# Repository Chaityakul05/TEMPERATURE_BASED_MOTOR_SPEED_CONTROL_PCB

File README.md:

# Temperature-Based DC Motor Speed Control

## Overview

This project focuses on controlling the speed of a DC motor based on the ambient temperature. The system utilizes a combination of analog and digital components: the **LM35** temperature sensor for temperature measurement, the **LM358** Op-Amp for comparing the sensor output with a reference voltage, the **555 Timer IC** to generate a PWM signal, and the **L293D motor driver** to control the motor's speed. As the temperature increases, the PWM signal's duty cycle increases, causing the motor to run faster.

## Key Components

- **LM35**: A temperature sensor that outputs an analog voltage proportional to the ambient temperature, with a sensitivity of 10 mV per °C.
- **LM358**: An operational amplifier configured as a comparator to compare the temperature sensor's output with a reference voltage set by a **potentiometer**.
- **555 Timer IC**: A timer IC configured in astable mode to generate a continuous PWM signal. The duty cycle of this signal is controlled by the output from the Op-Amp.
- **L293D**: A motor driver IC used to drive the DC motor by adjusting the voltage applied to the motor based on the PWM signal.
- **DC Motor**: The motor whose speed is controlled by the PWM signal generated by the 555 Timer and regulated by the L293D motor driver.
- **Potentiometer**: Used to set the reference voltage for the comparison with the LM35 output, determining the threshold temperature at which the motor speed increases.

## Working Principle

1. **Temperature Measurement**: The **LM35** temperature sensor detects the ambient temperature and generates a voltage output that is linearly proportional to the temperature (e.g., 250 mV at 25°C).
   
2. **Signal Comparison**: The **LM358 Op-Amp** compares the output from the **LM35** with a reference voltage set by the **potentiometer**. When the temperature exceeds the threshold set by the potentiometer, the Op-Amp output switches states.
   
3. **PWM Signal Generation**: The output of the **LM358** Op-Amp is used to control the **555 Timer IC**'s duty cycle. The **555 Timer** generates a PWM signal in astable mode, where the duty cycle is determined by the Op-Amp output. As the temperature rises, the Op-Amp output increases the PWM duty cycle, resulting in a faster motor speed.
   
4. **Motor Speed Control**: The PWM signal generated by the **555 Timer** is fed to the **L293D motor driver**, which adjusts the speed of the **DC motor**. The motor speed increases with higher temperature due to the higher PWM duty cycle.

## Circuit Setup

1. **Temperature Sensing**: The **LM35** is connected to a power supply (typically 5V). Its output is connected to the non-inverting input of the **LM358** Op-Amp.
   
2. **Reference Voltage**: The reference voltage is set using the **potentiometer**. The wiper of the potentiometer is connected to the inverting input of the **LM358**.
   
3. **PWM Signal Generation**: The output of the **LM358** is connected to the control voltage pin (pin 5) of the **555 Timer IC**, adjusting the duty cycle of the PWM signal generated by the timer.
   
4. **Motor Control**: The PWM signal from the **555 Timer** is fed into the **L293D motor driver**, which regulates the power supplied to the **DC motor** based on the PWM signal, controlling the motor speed according to the temperature.

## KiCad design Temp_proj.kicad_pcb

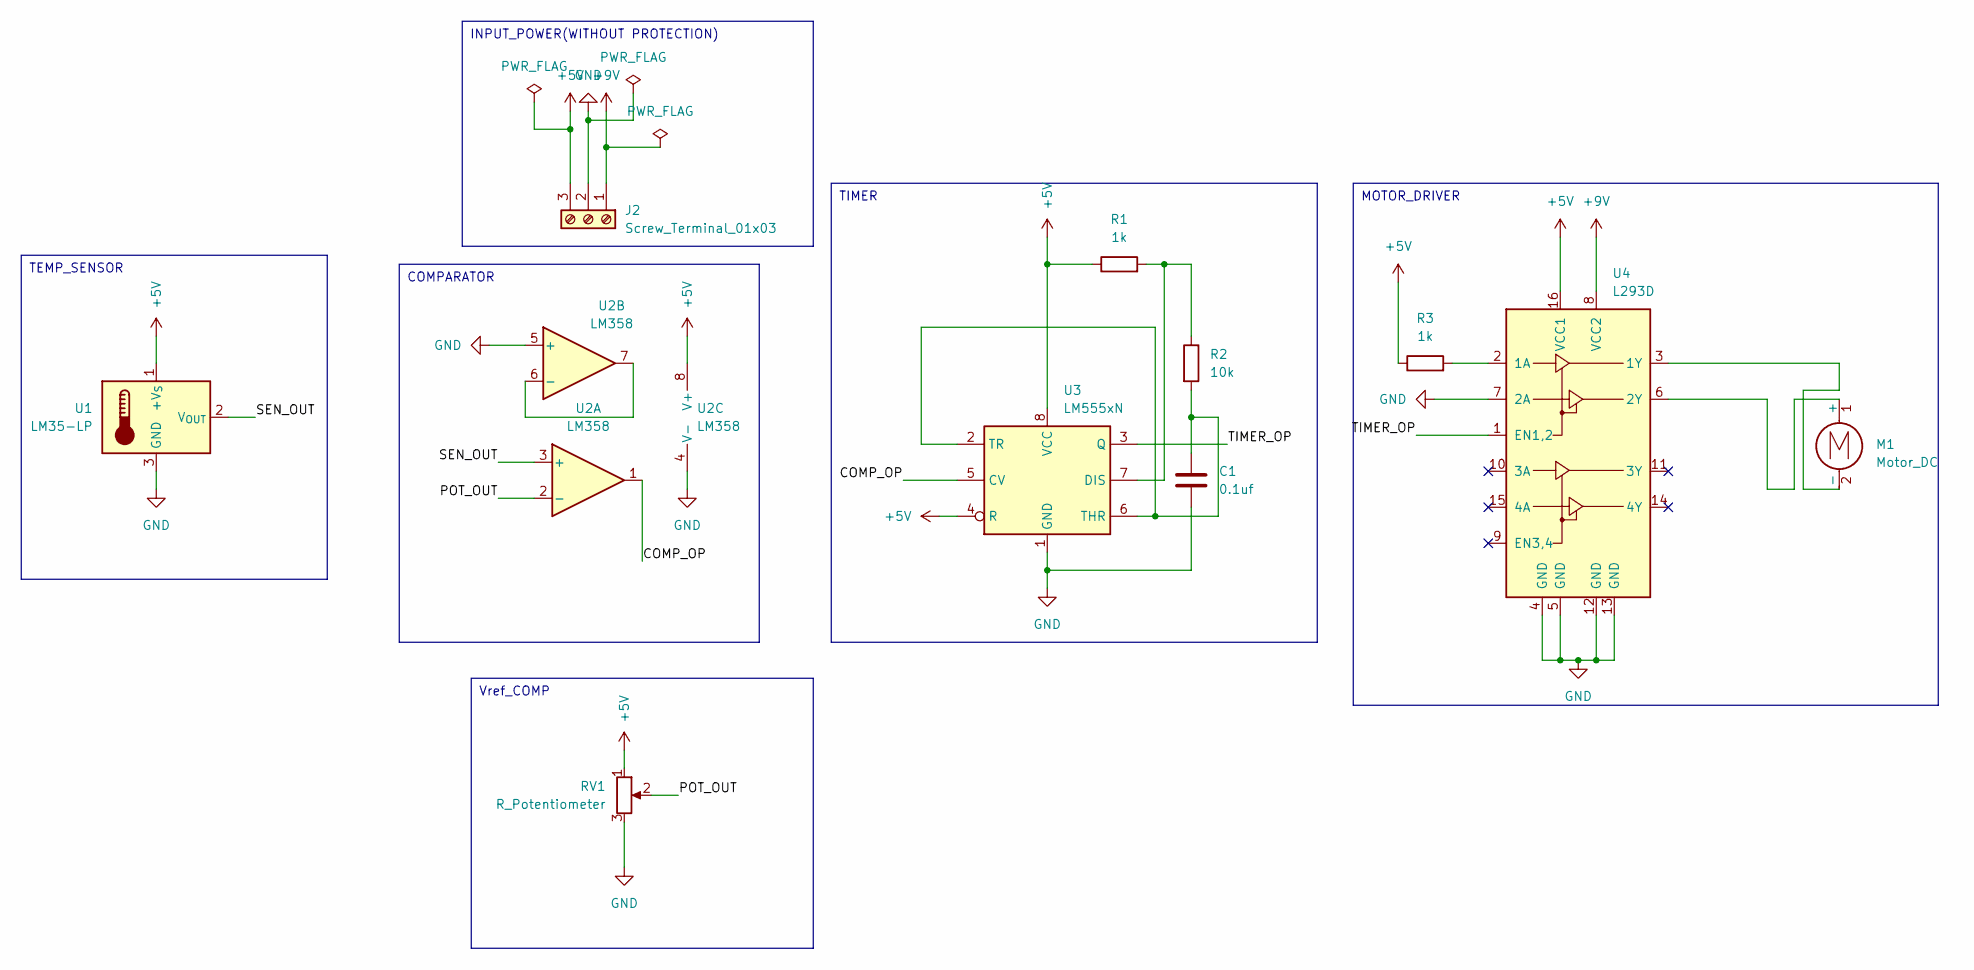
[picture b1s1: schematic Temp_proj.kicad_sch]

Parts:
C1: 0.1uf; C_Disc_D5.0mm_W2.5mm_P2.50mm
J2: Screw_Terminal_01x03; TerminalBlock_Altech_AK300-3_P5.00mm
M1: Motor_DC; PinHeader_1x02_P2.54mm_Horizontal
R1, R3: 1k; R_Axial_DIN0207_L6.3mm_D2.5mm_P10.16mm_Horizontal
R2: 10k; R_Axial_DIN0207_L6.3mm_D2.5mm_P10.16mm_Horizontal
RV1: R_Potentiometer; Potentiometer_Bourns_3296W_Vertical
U1: LM35-LP; TO-92_Inline
U2: LM358; DIP-8_W7.62mm
U3: LM555xN; DIP-8_W7.62mm
U4: L293D; DIP-16_W7.62mm

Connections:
+5V: J2.3, R1.1, R3.1, RV1.1, U1.1 (+V_{S}), U2.8 (V+), U3.4 (R), U3.8 (VCC), U4.16 (VCC1)
+9V: J2.1, U4.8 (VCC2)
/COMP_OP: U2.1, U3.5 (CV)
/POT_OUT: RV1.2, U2.2 (-)
/SEN_OUT: U1.2 (V_{OUT}), U2.3 (+)
/TIMER_OP: U3.3 (Q), U4.1 (EN1,2)
GND: C1.2, J2.2, RV1.3, U1.3 (GND), U2.4 (V-), U2.5 (+), U3.1 (GND), U4.4 (GND), U4.5 (GND), U4.7 (2A), U4.12 (GND), U4.13 (GND)
unnamed: M1.1 (+), U4.6 (2Y)
unnamed: M1.2 (-), U4.3 (1Y)
unnamed: U2.6 (-), U2.7
unnamed: R1.2, R2.1, U3.7 (DIS)
unnamed: C1.1, R2.2, U3.2 (TR), U3.6 (THR)
unnamed: R3.2, U4.2 (1A)

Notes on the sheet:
COMPARATOR
TIMER
TEMP_SENSOR
Vref_COMP
MOTOR_DRIVER
INPUT_POWER(WITHOUT PROTECTION)

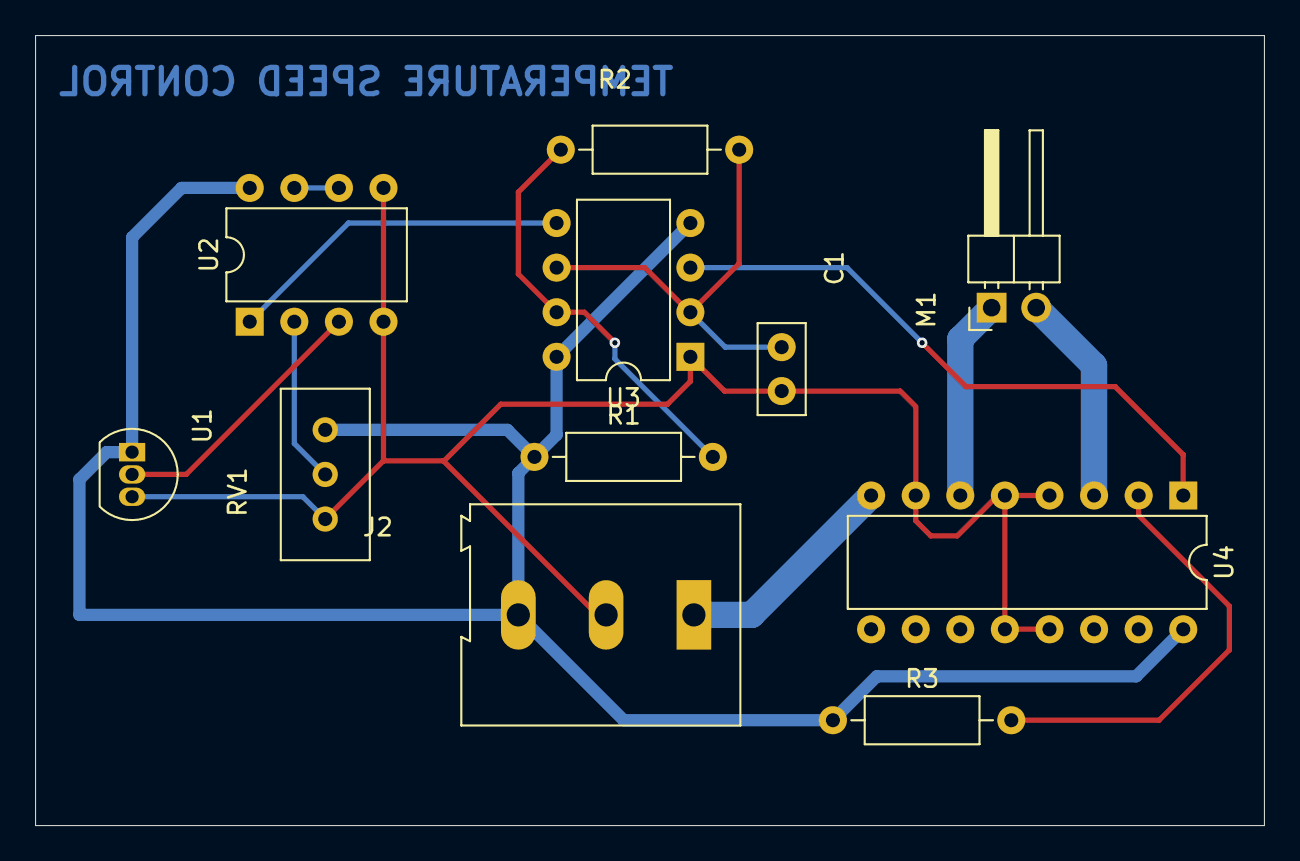
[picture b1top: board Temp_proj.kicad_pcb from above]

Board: 2 copper layers, 70.0 x 45.0 mm, 11 parts (0 on the bottom side), 13 nets.
